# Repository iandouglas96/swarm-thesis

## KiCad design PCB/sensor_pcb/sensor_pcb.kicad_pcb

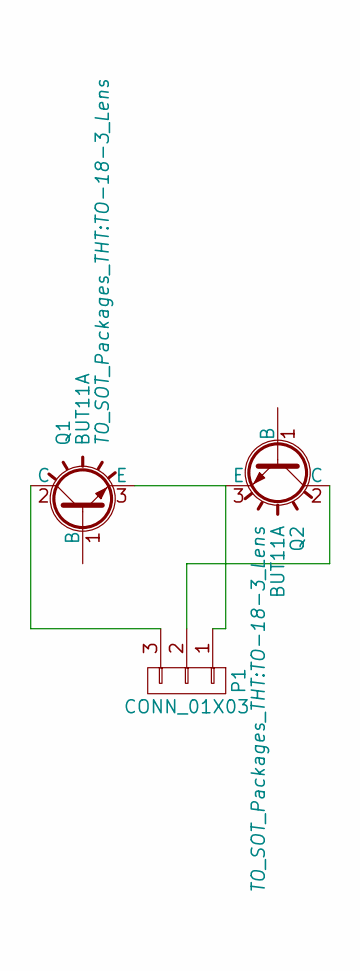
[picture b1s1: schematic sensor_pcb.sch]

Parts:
P1: CONN_01X03; Pin_Header_Angled_1x03_Pitch2.54mm
Q1, Q2: BUT11A; TO-18-3_Lens

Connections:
unnamed: P1.1, Q1.3 (E), Q2.3 (E)
unnamed: P1.2, Q2.2 (C)
unnamed: P1.3, Q1.2 (C)

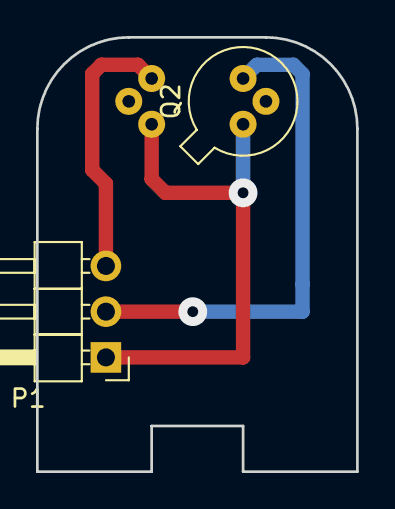
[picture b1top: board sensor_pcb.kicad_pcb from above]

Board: 2 copper layers, 17.8 x 24.1 mm, 3 parts (1 on the bottom side), 3 nets.

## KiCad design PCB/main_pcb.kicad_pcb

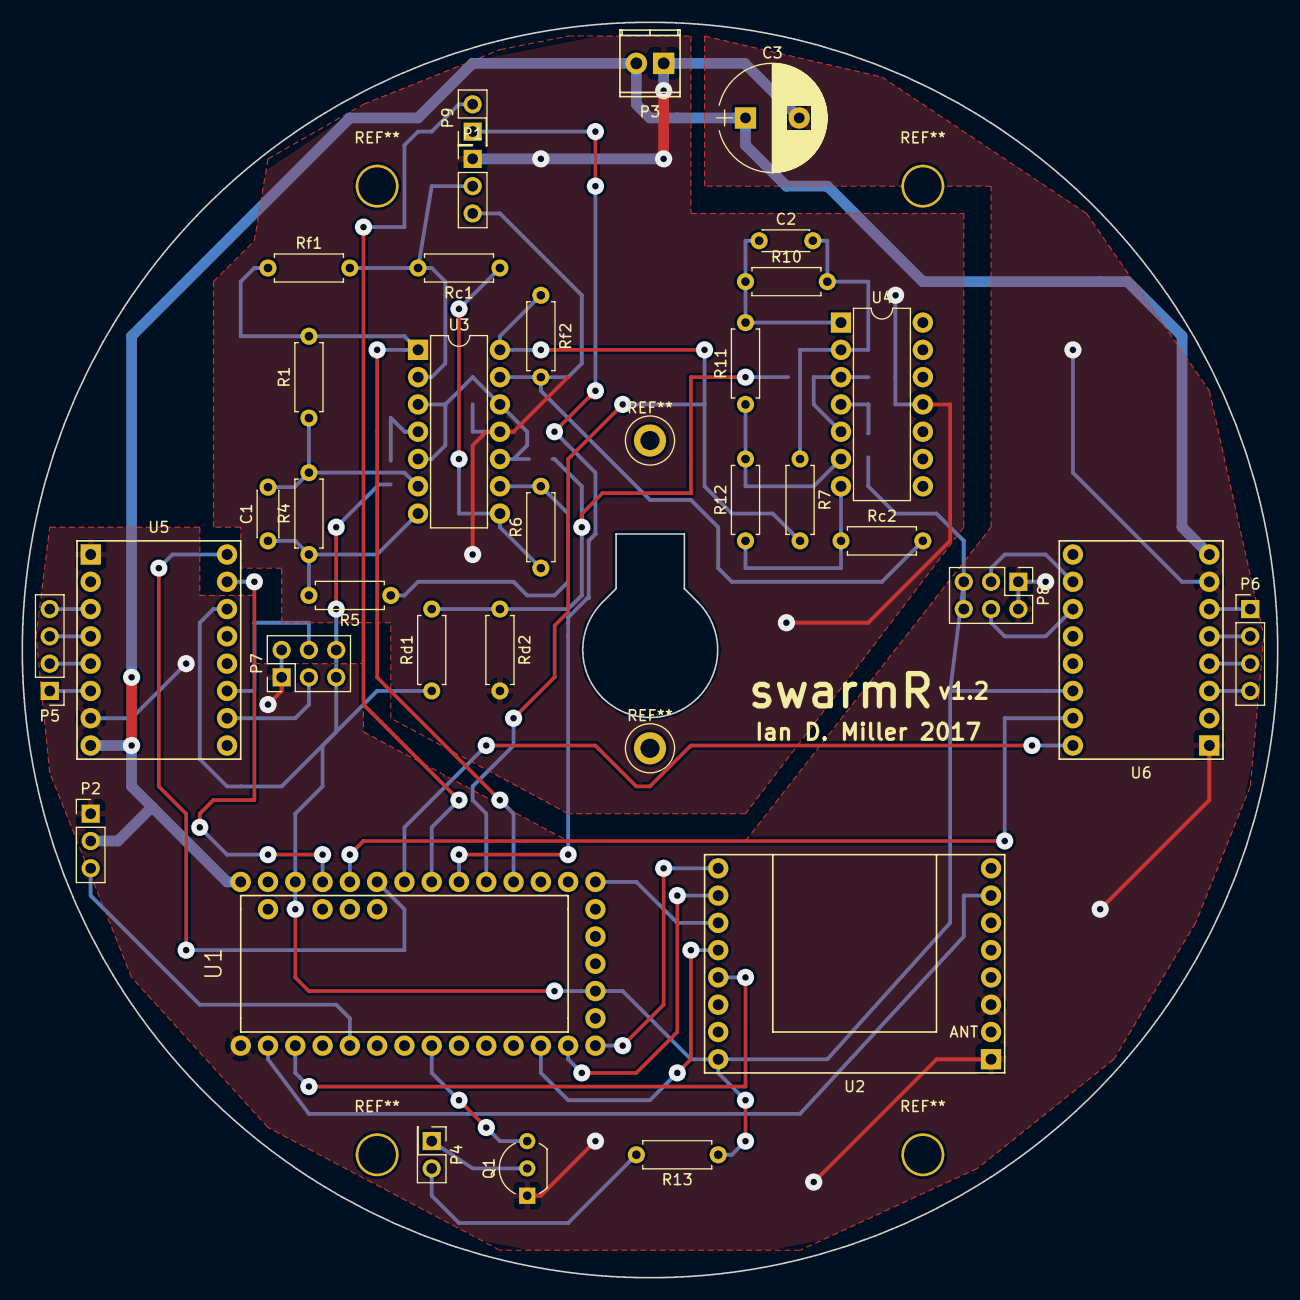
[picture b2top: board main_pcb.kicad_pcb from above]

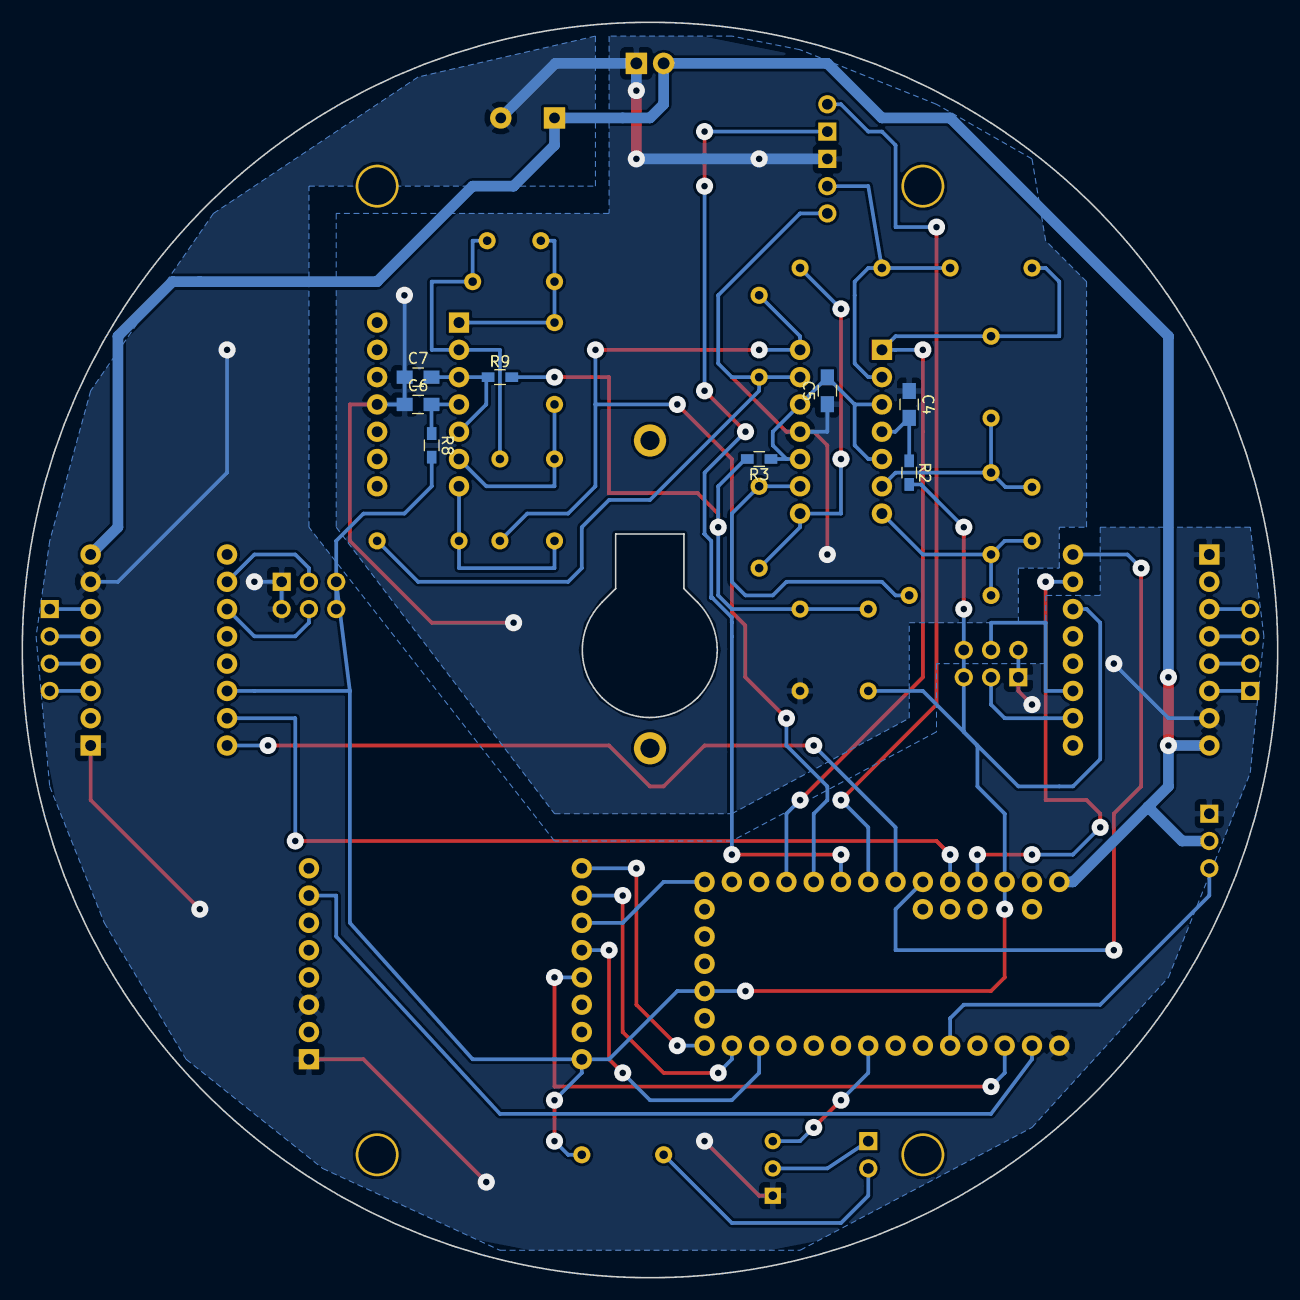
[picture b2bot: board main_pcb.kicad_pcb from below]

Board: 2 copper layers, 116.9 x 116.9 mm, 42 parts (8 on the bottom side), 46 nets.

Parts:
C1, C2: 0.47uF; C_Disc_D4.3mm_W1.9mm_P5.00mm
C3: 470uF; CP_Radial_D10.0mm_P5.00mm
C4, C5, C6, C7: 10u; C_0805_HandSoldering
P1: SEN; Pin_Header_Straight_1x03_Pitch2.54mm
P2: SRV; Pin_Header_Straight_1x03_Pitch2.54mm
P3: PWR; TerminalBlock_Pheonix_MPT-2.54mm_2pol
P4: LED; Pin_Header_Straight_2x01_Pitch2.54mm
P5: M1; Pin_Header_Straight_1x04_Pitch2.54mm
P6: M2; Pin_Header_Straight_1x04_Pitch2.54mm
P7, P8: CONN_02X03; Pin_Header_Straight_2x03_Pitch2.54mm
P9: Range; Pin_Header_Straight_2x01_Pitch2.54mm
Q1: 5LN01SP; TO-92_Inline_Wide
R1, R5, R6, R7, R11, R12: 20k; R_Axial_DIN0207_L6.3mm_D2.5mm_P7.62mm_Horizontal
R2, R8: 500; R_0603_HandSoldering
R3, R9: 10k; R_0603_HandSoldering
R4, R10: 1M; R_Axial_DIN0207_L6.3mm_D2.5mm_P7.62mm_Horizontal
R13: 10R; R_Axial_DIN0207_L6.3mm_D2.5mm_P7.62mm_Horizontal
Rc1, Rc2: 36k; R_Axial_DIN0207_L6.3mm_D2.5mm_P7.62mm_Horizontal
Rd1: 6.2k; R_Axial_DIN0207_L6.3mm_D2.5mm_P7.62mm_Horizontal
Rd2: 1.5k; R_Axial_DIN0207_L6.3mm_D2.5mm_P7.62mm_Horizontal
Rf1, Rf2: 68k; R_Axial_DIN0207_L6.3mm_D2.5mm_P7.62mm_Horizontal
U1: Teensy_3.1; Teensy-3.1
U2: RFM69_Breakout; RFM69Breakout
U3, U4: MCP6004; DIP-14_W7.62mm_Socket
U5, U6: DRV8834_Breakout; DRV8834Breakout

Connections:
3v3f: C4.2, C6.2, R2.1, R8.1, U3.4, U4.4
+3V3: P7.5, P7.6, P8.5, P8.6, R2.2, R8.2, R13.1, Rd1.1, U1.24, U1.31, U2.8, U5.6, U6.6
/DIR1: U1.21, U5.8
/DIR2: U1.20, U6.8
/FFT1: R1.2, Rf1.1, U1.16, U3.1
/FFT2: R7.2, Rf2.1, U1.17, U3.14
/LED: Q1.3, U1.6
/MISO: U1.12, U2.1
/MOSI: U1.11, U2.2
/RadCS: U1.10, U2.4
/RadInt: U1.0, U2.15
/Reset: U1.1, U2.5
/SCK: U1.13, U2.3
/SRV: P2.3, U1.3
/STEP1: U1.23, U5.7
/STEP2: U1.22, U6.7
/Sen1: P1.2, Rc1.2, Rf1.2, U3.2
/Sen2: P1.3, Rc2.2, Rf2.2, U3.13
/Vref: R3.2, R9.2, Rd1.2, Rd2.1
GND: C3.2, C4.1, C5.1, C6.1, C7.1, P1.1, P2.1, P3.1, P7.1, P7.2, P8.1, P8.2, Q1.1, Rd2.2, U1.27, U2.9, U2.11, U3.11, U4.11, U5.9, U5.15, U6.9, U6.15
unnamed: C1.1, R4.1, R5.2, U3.7
unnamed: C1.2, R1.1, R4.2, U3.6
unnamed: C2.1, R10.1, R11.2, U4.1
unnamed: C2.2, R7.1, R10.2, U4.2
unnamed: P4.1, Q1.2
unnamed: P4.2, R13.2
unnamed: P5.1, U5.14
unnamed: P5.2, U5.13
unnamed: P5.3, U5.12
unnamed: P5.4, U5.11
unnamed: P6.1, U6.14
unnamed: P6.2, U6.13
unnamed: P6.3, U6.12
unnamed: P6.4, U6.11
unnamed: P7.3, U5.2
unnamed: P7.4, U5.3
unnamed: P8.3, U6.2
unnamed: P8.4, U6.3
unnamed: P9.1, U1.18
unnamed: P9.2, U1.19
unnamed: R5.1, R6.2, U3.9
unnamed: R6.1, Rc1.1, U3.8
unnamed: R11.1, R12.2, U4.6
unnamed: R12.1, Rc2.1, U4.7
VDD: C3.1, P2.2, P3.2, U1.26, U5.16, U6.16
ref_filter: C5.2, C7.2, R3.1, R9.1, U3.3, U3.5, U3.10, U3.12, U4.3, U4.5

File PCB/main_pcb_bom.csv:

"Id";"Designator";"Package";"Quantity";"Designation";"Supplier and ref";
1;"REF**,REF**,REF**,REF**";"MountingHole_3.5mm_Pad";4;"Mount";;;
2;"REF**,REF**";"1pin";2;"1pin";;;
3;"C1,C2";"C_Disc_D4.3mm_W1.9mm_P5.00mm";2;"0.47uF";;;
4;"C3";"CP_Radial_D10.0mm_P5.00mm";1;"470uF";;;
5;"P1";"Pin_Header_Straight_1x03_Pitch2.54mm";1;"SEN";;;
6;"P2";"Pin_Header_Straight_1x03_Pitch2.54mm";1;"SRV";;;
7;"P3";"TerminalBlock_Pheonix_MPT-2.54mm_2pol";1;"PWR";;;
8;"P4";"Pin_Header_Straight_2x01_Pitch2.54mm";1;"LED";;;
9;"P5";"Pin_Header_Straight_1x04_Pitch2.54mm";1;"M1";;;
10;"P6";"Pin_Header_Straight_1x04_Pitch2.54mm";1;"M2";;;
11;"Q1";"TO-92_Inline_Wide";1;"5LN01SP";;;
12;"R1,R5,R6,R7,R11,R12";"R_Axial_DIN0207_L6.3mm_D2.5mm_P7.62mm_Horizontal";6;"20k";;;
13;"R4,R10";"R_Axial_DIN0207_L6.3mm_D2.5mm_P7.62mm_Horizontal";2;"1M";;;
14;"R13";"R_Axial_DIN0207_L6.3mm_D2.5mm_P7.62mm_Horizontal";1;"10R";;;
15;"Rc1,Rc2";"R_Axial_DIN0207_L6.3mm_D2.5mm_P7.62mm_Horizontal";2;"36k";;;
16;"Rd1";"R_Axial_DIN0207_L6.3mm_D2.5mm_P7.62mm_Horizontal";1;"6.2k";;;
17;"Rd2";"R_Axial_DIN0207_L6.3mm_D2.5mm_P7.62mm_Horizontal";1;"1.5k";;;
18;"Rf1,Rf2";"R_Axial_DIN0207_L6.3mm_D2.5mm_P7.62mm_Horizontal";2;"68k";;;
19;"U1";"Teensy-3.1";1;"Teensy_3.1";;;
20;"U3,U4";"DIP-14_W7.62mm";2;"MCP6004";;;
21;"P7,P8";"Pin_Header_Straight_2x03_Pitch2.54mm";2;"CONN_02X03";;;
22;"U6,U5";"DRV8834Breakout";2;"DRV8834_Breakout";;;
23;"U2";"RFM69Breakout";1;"RFM69_Breakout";;;
24;"P9";"Pin_Header_Straight_2x01_Pitch2.54mm";1;"Range";;;

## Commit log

2017-06-15 Added arduino code
2017-06-15 Reorganized Arduino code to point the IDE in the right place
2017-06-15 Added supporting PCB layouts
2017-06-16 Added simulation code to repo
2017-06-16 Added code to track both ffts simultaneously
2017-06-16 Updated visualizer for 360
2017-06-16 Incremental: adding motor control
2017-06-19 Added stepper controller to arduino code
2017-06-19 Added scanning delays. NOTE: this breaks walls for the time being
2017-06-19 Simulation now includes drive constrints
2017-06-20 Improved simulation, did most of the pcb trace layout
2017-06-20 Improved peak detection algorithm, switched to using op505d part
2017-06-21 Pulled in RFM69 library, modified to support teensy
2017-06-21 Pointed RFM69 module at corrent fork
2017-06-21 Finished PCB and robot designs
2017-06-21 Added kerf compensation to inventor models
2017-06-21 Minor adjustments to laser outlines
2017-06-22 Updated pcb layout for easier fabrication
2017-06-23 minor pcb and BOM adjustments
2017-06-26 Small pcb adjustments
2017-06-28 Added force computation
2017-06-28 functioning with static targets!
2017-07-03 Added wireless command format proposed doc
2017-07-03 Markdown adjustments
2017-07-03 Incremental: adding wireless command capabilities. DOES NOT COMPILE
2017-07-04 Compiling with EEPROM load/save
2017-07-04 Functioning wireless communication framework
2017-07-04 Incremental: Building control application
2017-07-05 Functioning python serial receiving driver
2017-07-05 GUI list of scanned robots working
2017-07-05 Cleaned up kivy code, have nice working selectable list
2017-07-05 Working metadata display
2017-07-05 Switched to transmitting length instead of using null terminator
2017-07-05 Incremental: working on getting settable values
2017-07-06 Functioning dump and sent_configs from gui
2017-07-06 Cleaned up git repo for mac
2017-07-06 Rewrote controller to now use a node class, which makes things much cleaner
2017-07-06 Working manual control
2017-07-06 Adjustments to arduino code to support manual control
2017-07-06 Updated controller to handle new formatting for commands
2017-07-06 Added length tag to the front of messages transmitted to computer from receiver
2017-07-07 Added status update functionality
2017-07-07 Pulled in new RFM69 library, have functional test sketch
2017-07-07 Incremental: switching to new RFM69 library
2017-07-07 switched to new rfm69 library mostly complete
2017-07-07 Controller adjustments for new rfm69 library
2017-07-10 Functional update framework
2017-07-10 Arduino side stuff to fix updates
2017-07-11 Parsing target list update packets
2017-07-11 Implemented ACKing and drawing
2017-07-11 ACKing support stuff
2017-07-11 added calib info
2017-07-11 redid calib
2017-07-11 rewriting detection code
2017-07-12 Rewrote target peak detection algorithm
2017-07-12 calibration adjustments
2017-07-12 PCB revisions
2017-07-13 Began to build sim backend
2017-07-13 Functioning animations for sim
2017-07-13 Incremental: adding virtual force computation to sim
2017-07-13 Functioning swarm movement
2017-07-17 Updated sensor pcb to use nte3037 part
2017-07-17 Recalibrated resistor gains
2017-07-17 Sensor pcb redesign. Fixed bug where teensy would freeze if there were more than 10 targets
2017-07-19 Debugging tweaks
2017-07-19 debugging tweaks, bug fixes for receiver
2017-07-21 New peak detection algorithm to merge peake too close to eachother
2017-07-21 Added tx timeout to transmitter to avoid buffer getting in weird state
2017-07-21 Reworked manual mode, added frequency to eeprom
2017-07-21 Reworked scanning code so existing objects are updated and not destroyed. Other small adjustments to make interface less obtuse
2017-07-21 Added copper pours
2017-07-24 Functioning comm link b/w controller and sim
2017-07-24 pcb tweaks
2017-07-25 Working manual movement commands in sim
2017-08-02 Working auto mode
2017-09-05 Refined sim calibration
2017-09-05 Working updates in sim
2017-09-14 Added display of node info
2017-09-20 Working global positions calculations in sandbox
2017-09-20 Working npy output from sim, input into position calc
2017-09-25 Now locally generate and process random swarm configurations
2017-09-27 Autogenerate config for testing
2017-10-01 Added code for positioning characterization
2017-10-02 Added simple location integration to control software
2017-10-05 Major performance improvements in numpy code
2017-10-19 Working simple EKFKF
2017-10-26 Loosely working implemented EKF with simulation
2017-11-11 Working UKF
2017-11-11 Extended UKF to handle varying landmark array sizes
2017-11-11 UKF integrated into controller
2017-11-29 Fixed PSD error
2017-11-30 Small updates
2017-12-05 Switched to sending distance data over wireless instead of magnitude
2017-12-05 Added sensor calibration to EEPROM on a per-robot basis. Now transmit distance in cm in verbose mode instead of sensor return magnitude
2018-01-22 Fixed bug with ordering of robots when scanning in the minimization state
2018-01-28 Began work on image tracking system
2018-02-02 Added code to generate 4-square aruco board for robots
2018-02-04 Getting pos/orientation readinggs out of opencv
2018-02-08 In progress integration of motion capture system into control software
2018-02-08 Rendering robot locations in OpenCV
2018-02-08 Now rendering detected and calculated robot orientations
2018-02-09 Working comparison b/w mcap and sensor system
2018-02-12 Working with 3 robots
2018-02-22 Tweaks for logging data to file for later analysis
2018-02-23 Fine calibration adjustments
2018-03-02 Fixed some motor speed modelling errors
2018-03-02 More improvement of motion model
2018-03-07 Added comparison with minimization algorithm in real time. Lots of bug fixes in minimization algorithm and kalman filter models having to do with coordinate system problems (particularly signs of ang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
2018-03-29 Updated simulator to work with fixed coordinate system in hardware
2018-03-29 Cosmetic adjustments for simulator, added kivy #:kivy to make linter happy
2018-03-29 Added framework for timed preset command execution
2018-03-29 Working automatic formation control
2018-04-04 Added several preset test cases
2018-04-26 Added support for 5 HW robots and frequencies
2018-04-29 Updated to support up to 5 HW robots
2018-05-01 Check and block data indicating robot seeing itself, which destabilized ukf
2018-05-07 Final commit after presentation
2018-05-08 Create LICENSE
